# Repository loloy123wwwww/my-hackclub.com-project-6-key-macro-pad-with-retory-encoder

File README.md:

Here is my first project of macropad i made it in Kicad and fusion 360 it has 6 keys and 1 rotary encoder everything is powered by XIAO board firmware coded i  pythone using kmk library and board library that's pretty much everything

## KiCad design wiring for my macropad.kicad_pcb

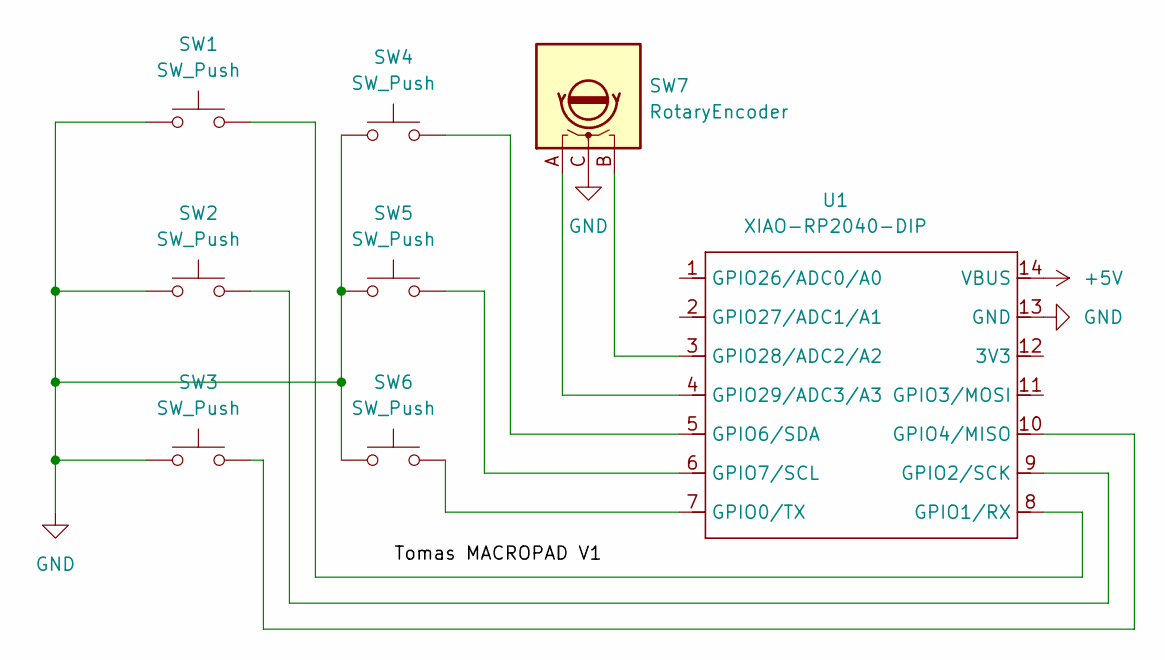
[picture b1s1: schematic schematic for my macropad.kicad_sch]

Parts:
SW1, SW2, SW3, SW4, SW5, SW6: SW_Push; SW_Cherry_MX_1.00u_PCB
SW7: RotaryEncoder; RotaryEncoder_Alps_EC11E_Vertical_H20mm
U1: XIAO-RP2040-DIP

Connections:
+5V: U1.14 (VBUS)
/SCL: U1.1 (GPIO26/ADC0/A0)
/SDA: U1.2 (GPIO27/ADC1/A1)
GND: SW1.1, SW2.1, SW3.1, SW4.1, SW5.1, SW6.1, SW7.C, U1.13 (GND)
unnamed: SW6.2, U1.7 (GPIO0/TX)
unnamed: SW1.2, U1.8 (GPIO1/RX)
unnamed: SW2.2, U1.9 (GPIO2/SCK)
unnamed: SW3.2, U1.10 (GPIO4/MISO)
unnamed: SW4.2, U1.5 (GPIO6/SDA)
unnamed: SW5.2, U1.6 (GPIO7/SCL)
unnamed: SW7.B, U1.3 (GPIO28/ADC2/A2)
unnamed: SW7.A, U1.4 (GPIO29/ADC3/A3)

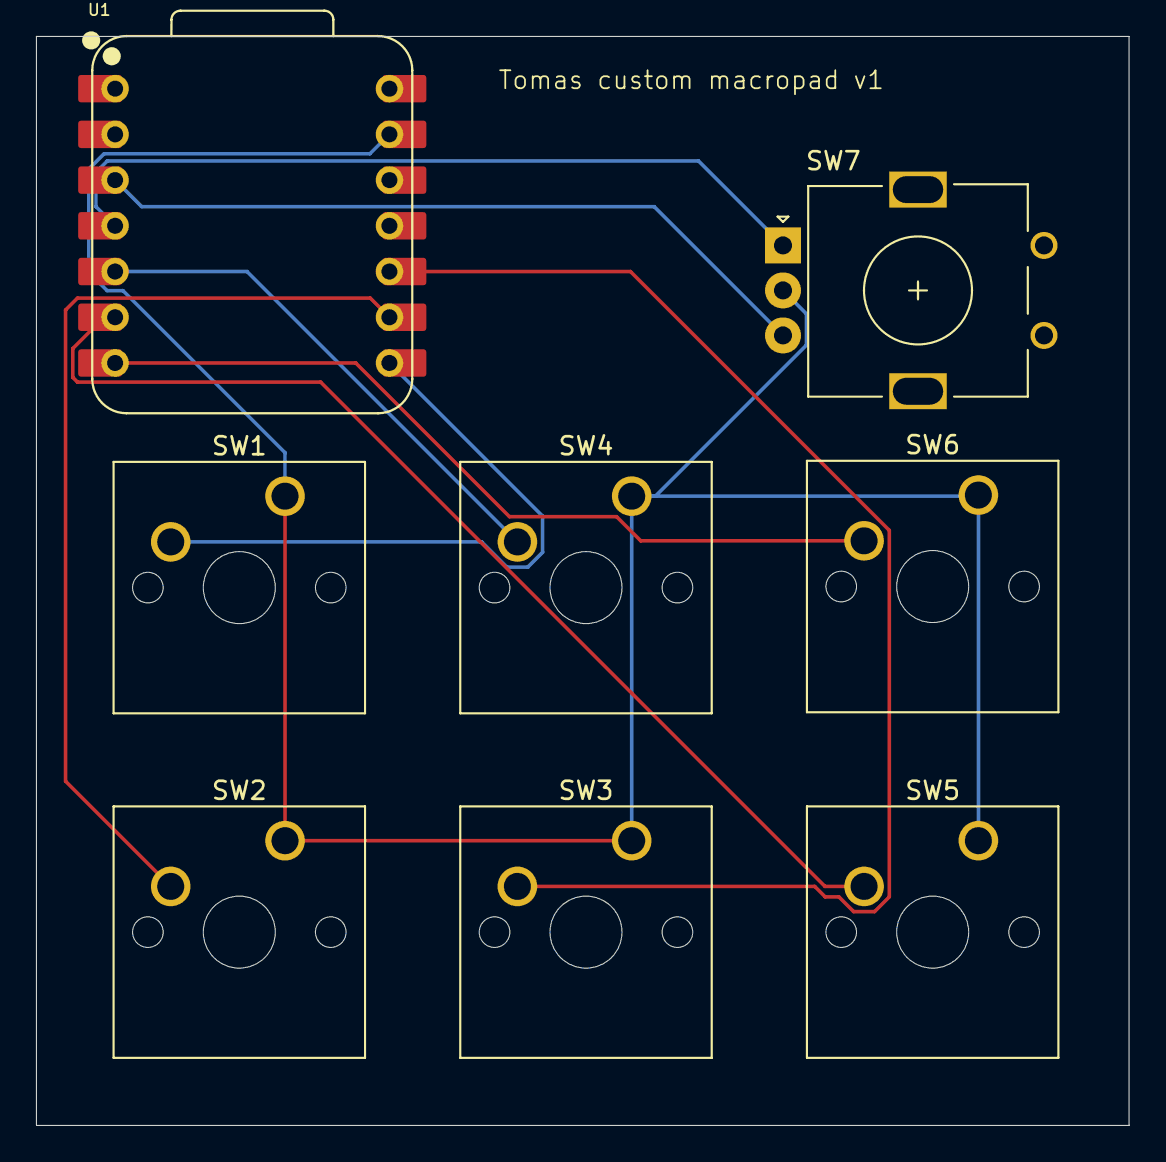
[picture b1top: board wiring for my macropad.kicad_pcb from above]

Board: 2 copper layers, 60.7 x 60.5 mm, 8 parts (0 on the bottom side), 9 nets.

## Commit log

2025-12-10 FIRMWARE
    my firmware
    -Tomas
2025-12-10 SCHEMATIC
    schematic in KiCad
2025-12-10 PCB file
    in this file theres wiring in PCB editor
2025-12-10 TOP part of the 3d design
2025-12-10 BOTTOM file of 3D design
2025-12-11 all important files
2025-12-11 PHOTOS
2025-12-11 CODE
2025-12-11 all kicad files
2025-12-11 for my 3D printer
2025-12-11 3D printer
2025-12-11 3D files
2025-12-11 ALL PARTS
2025-12-11 all parts pics
